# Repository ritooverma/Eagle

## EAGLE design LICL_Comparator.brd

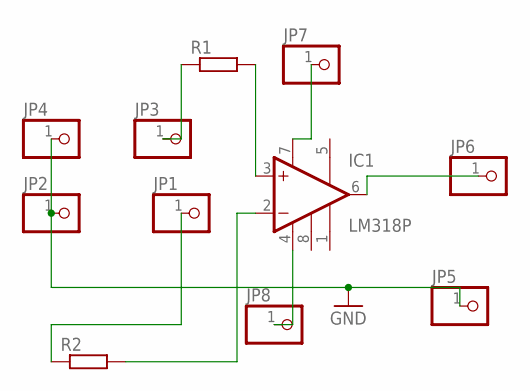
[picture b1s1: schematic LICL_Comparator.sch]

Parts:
IC1: LM318P; DIL08
JP1, JP2, JP3, JP4, JP5, JP6, JP7, JP8: PINHD-1X1; 1X01
R1, R2: R-EU_0207/10; 0207/10

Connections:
GND: JP2.1, JP4.1, JP5.1
unnamed: IC1.2 (-IN), R2.2
unnamed: IC1.3 (+IN), R1.2
unnamed: JP1.1, R2.1
unnamed: IC1.6 (OUT), JP6.1
unnamed: IC1.7 (V+), JP7.1
unnamed: IC1.4 (V-), JP8.1
unnamed: JP3.1, R1.1

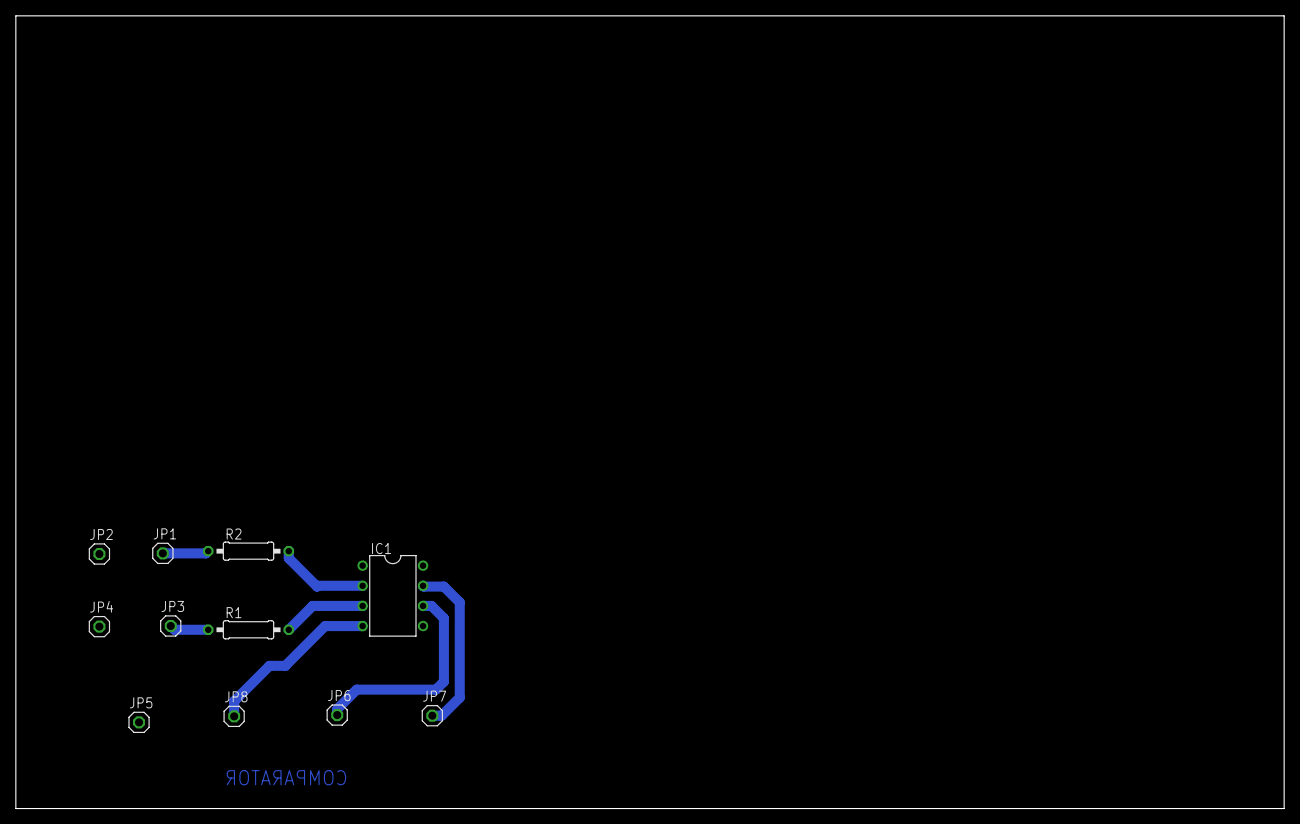
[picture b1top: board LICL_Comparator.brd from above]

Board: 2 copper layers, 160.0 x 100.0 mm, 11 parts (0 on the bottom side), 8 nets.

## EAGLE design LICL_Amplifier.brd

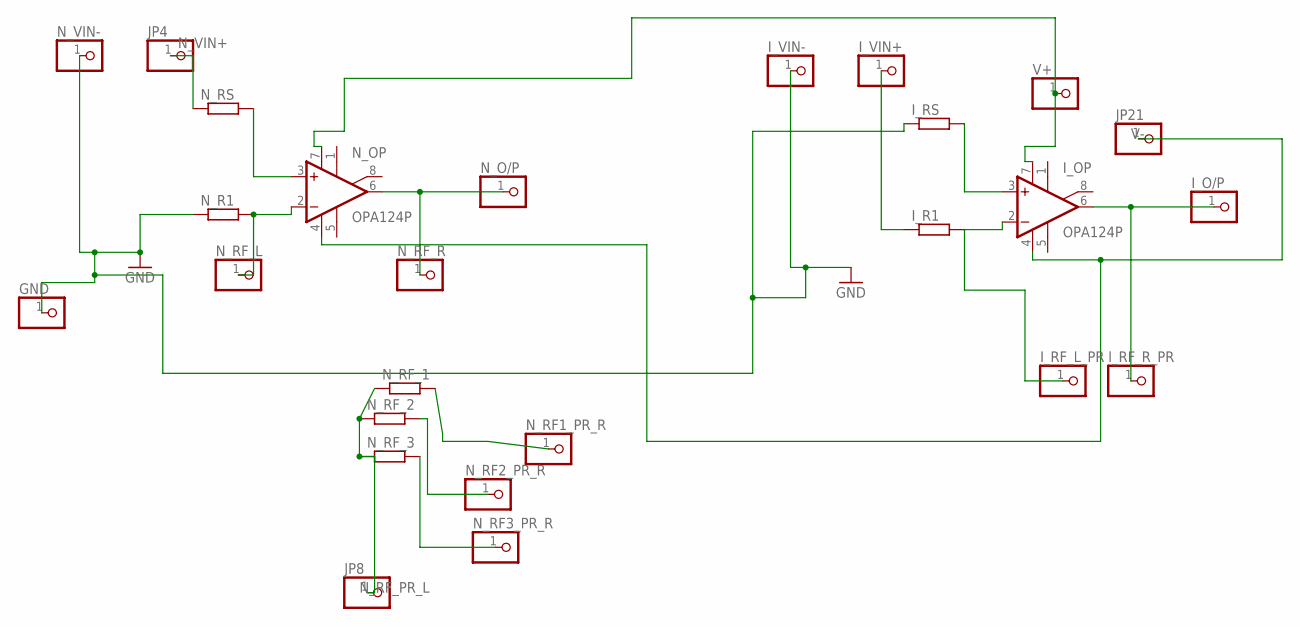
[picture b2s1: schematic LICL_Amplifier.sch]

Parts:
GND: PINHD-1X1; 1X01
I_O/P: PINHD-1X1; 1X01
I_OP: OPA124P; DIL08
I_R1: R-EU_0207/10; 0207/10
I_RF_L_PR: PINHD-1X1; 1X01
I_RF_R_PR: PINHD-1X1; 1X01
I_RS: R-EU_0207/10; 0207/10
I_VIN+: PINHD-1X1; 1X01
I_VIN-: PINHD-1X1; 1X01
JP4, JP8, JP21: PINHD-1X1; 1X01
N_O/P: PINHD-1X1; 1X01
N_OP: OPA124P; DIL08
N_R1: R-EU_0207/10; 0207/10
N_RF1_PR_R, N_RF2_PR_R, N_RF3_PR_R: PINHD-1X1; 1X01
N_RF_1, N_RF_2, N_RF_3: R-EU_0207/10; 0207/10
N_RF_L: PINHD-1X1; 1X01
N_RF_R: PINHD-1X1; 1X01
N_RS: R-EU_0207/10; 0207/10
N_VIN-: PINHD-1X1; 1X01
V+: PINHD-1X1; 1X01

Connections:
GND: GND.1, I_RS.1, I_VIN-.1, N_R1.1, N_VIN-.1
unnamed: N_OP.3 (+IN), N_RS.2
unnamed: N_O/P.1, N_OP.6 (OUT), N_RF_R.1
unnamed: N_RF1_PR_R.1, N_RF_1.2
unnamed: N_RF2_PR_R.1, N_RF_2.2
unnamed: N_RF3_PR_R.1, N_RF_3.2
unnamed: I_OP.7 (V+), N_OP.7 (V+), V+.1
unnamed: I_OP.3 (+IN), I_RS.2
unnamed: I_R1.1, I_VIN+.1
unnamed: I_OP.2 (-IN), I_R1.2, I_RF_L_PR.1
unnamed: I_O/P.1, I_OP.6 (OUT), I_RF_R_PR.1
N_RF_L: N_OP.2 (-IN), N_R1.2, N_RF_L.1
N_RF_PR_L: JP8.1, N_RF_1.1, N_RF_2.1, N_RF_3.1
N_VIN+: JP4.1, N_RS.1
V-: I_OP.4 (V-), JP21.1, N_OP.4 (V-)

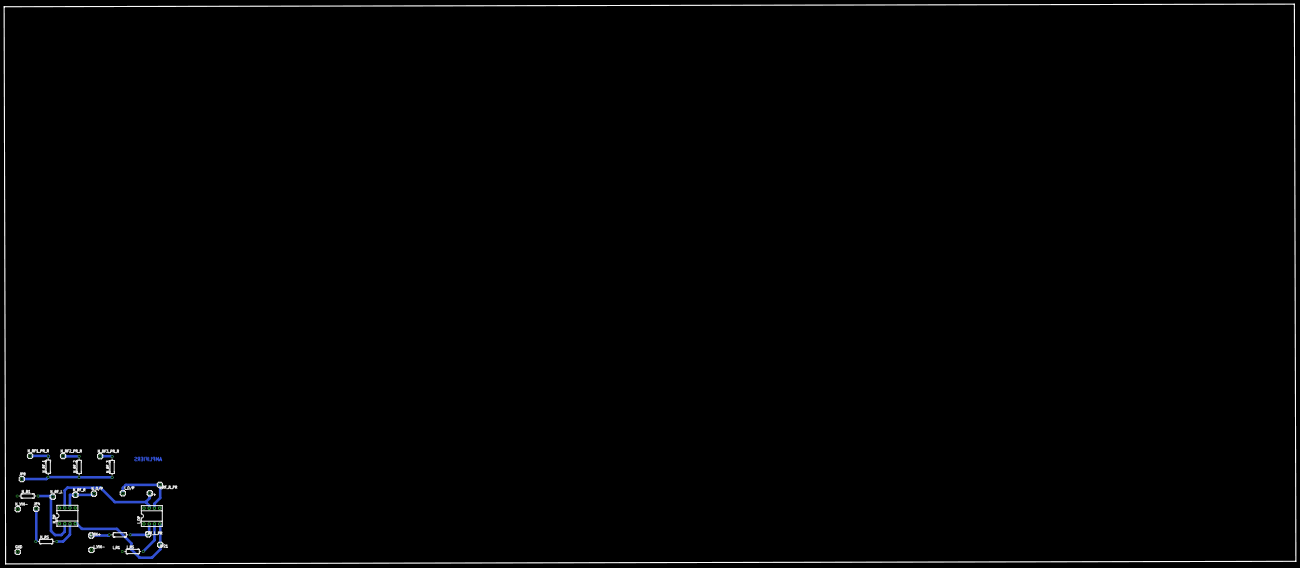
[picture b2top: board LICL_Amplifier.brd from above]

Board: 2 copper layers, 626.8 x 271.6 mm, 26 parts (0 on the bottom side), 15 nets.

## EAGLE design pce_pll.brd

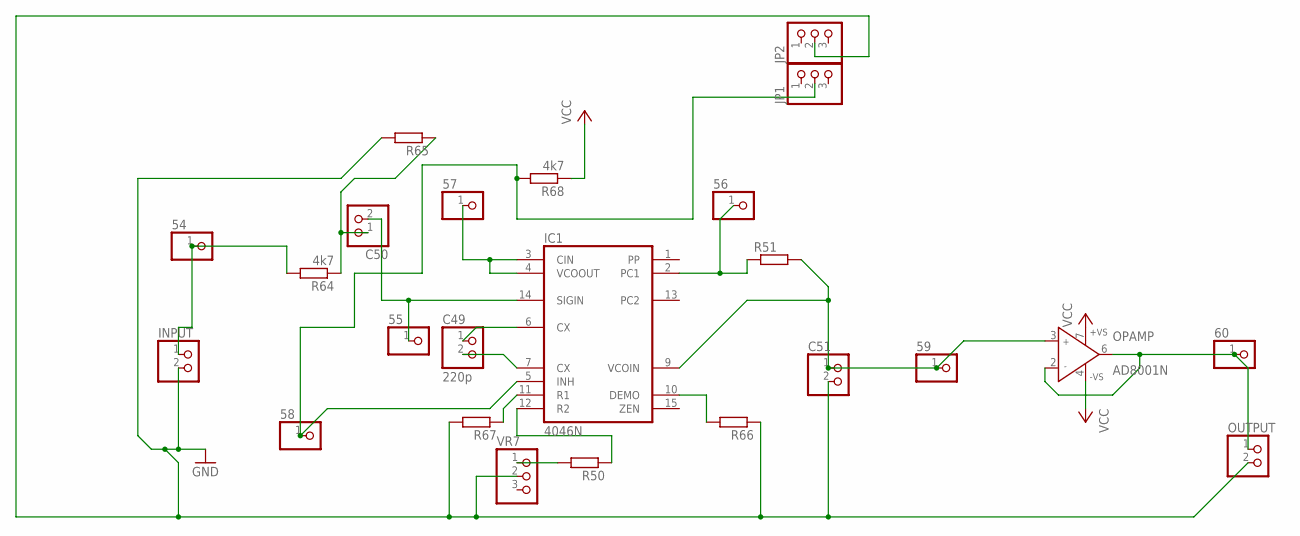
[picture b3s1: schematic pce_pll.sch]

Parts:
54, 55, 56, 57, 58, 59, 60: PINHD-1X1; 1X01
C49: 220p; 1X02
C50, C51: PINHD-1X2; 1X02
IC1: 4046N; DIL16
INPUT: PINHD-1X2; 1X02
JP1, JP2: PINHD-1X3; 1X03
OPAMP: AD8001N; DIL08
OUTPUT: PINHD-1X2; 1X02
R50, R51, R65, R66, R67: R-EU_0207/10; 0207/10
R64, R68: 4k7; 0207/10
VR7: PINHD-1X3; 1X03

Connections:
54: 54.1, INPUT.1, R64.2
GND: C51.2, INPUT.2, JP2.2, OUTPUT.2, R65.2, R66.1, R67.2, VR7.2
unnamed: 57.1, IC1.3 (CIN), IC1.4 (VCOOUT)
unnamed: 56.1, IC1.2 (PC1), R51.1
unnamed: IC1.10 (DEMO), R66.2
unnamed: 55.1, C50.2, IC1.14 (SIGIN)
unnamed: C50.1, R64.1, R65.1
unnamed: C49.1, IC1.6 (CX)
unnamed: C49.2, IC1.7 (CX)
unnamed: IC1.12 (R2), R50.1
unnamed: IC1.11 (R1), R67.1
unnamed: 60.1, OPAMP.2 (IN-), OPAMP.6 (OUT), OUTPUT.1
unnamed: 59.1, C51.1, IC1.9 (VCOIN), OPAMP.3 (IN+), R51.2
unnamed: 58.1, IC1.5 (INH), JP1.2, R68.2
unnamed: R50.2, VR7.1
VCC: OPAMP.4 (-VS), OPAMP.7 (+VS), R68.1
VDD: IC1.16 (VDD)
VSS: IC1.8 (VSS)

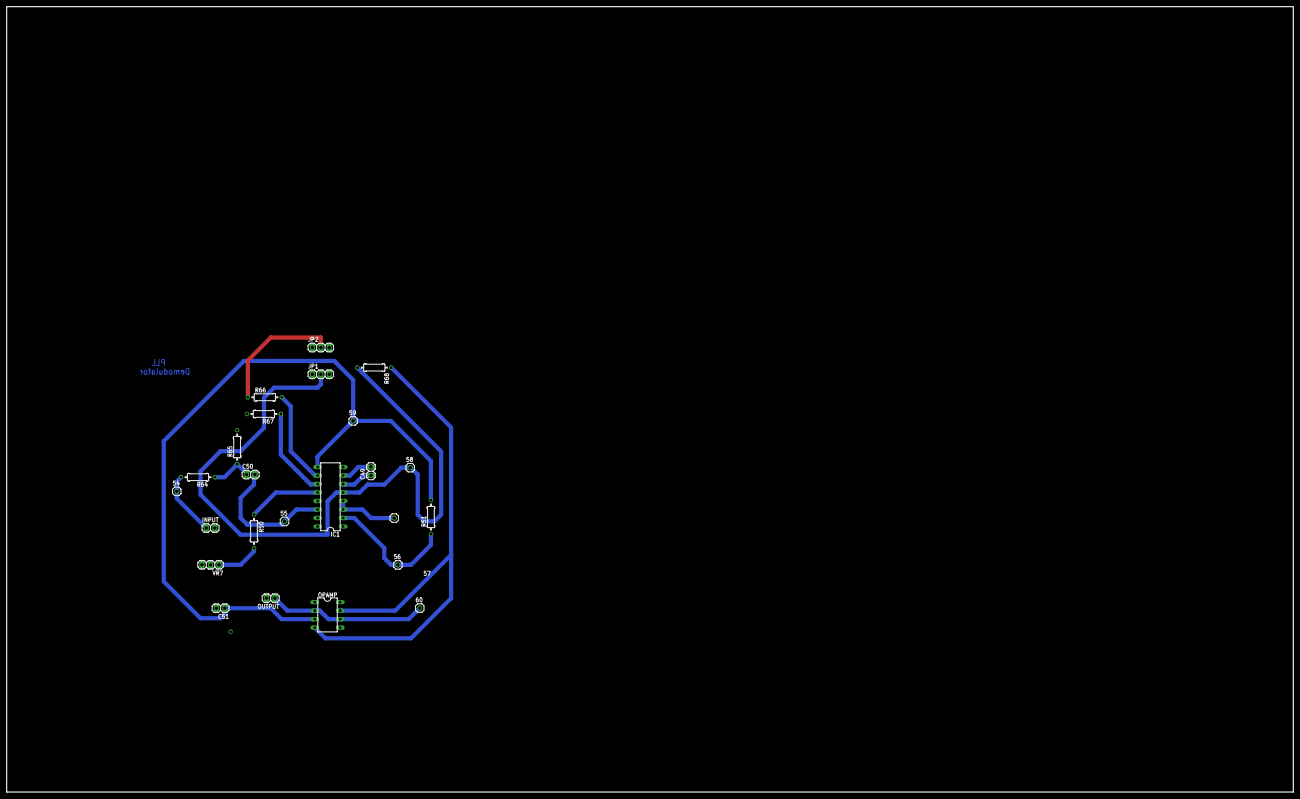
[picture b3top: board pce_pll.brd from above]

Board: 2 copper layers, 385.0 x 235.0 mm, 24 parts (0 on the bottom side), 16 nets.

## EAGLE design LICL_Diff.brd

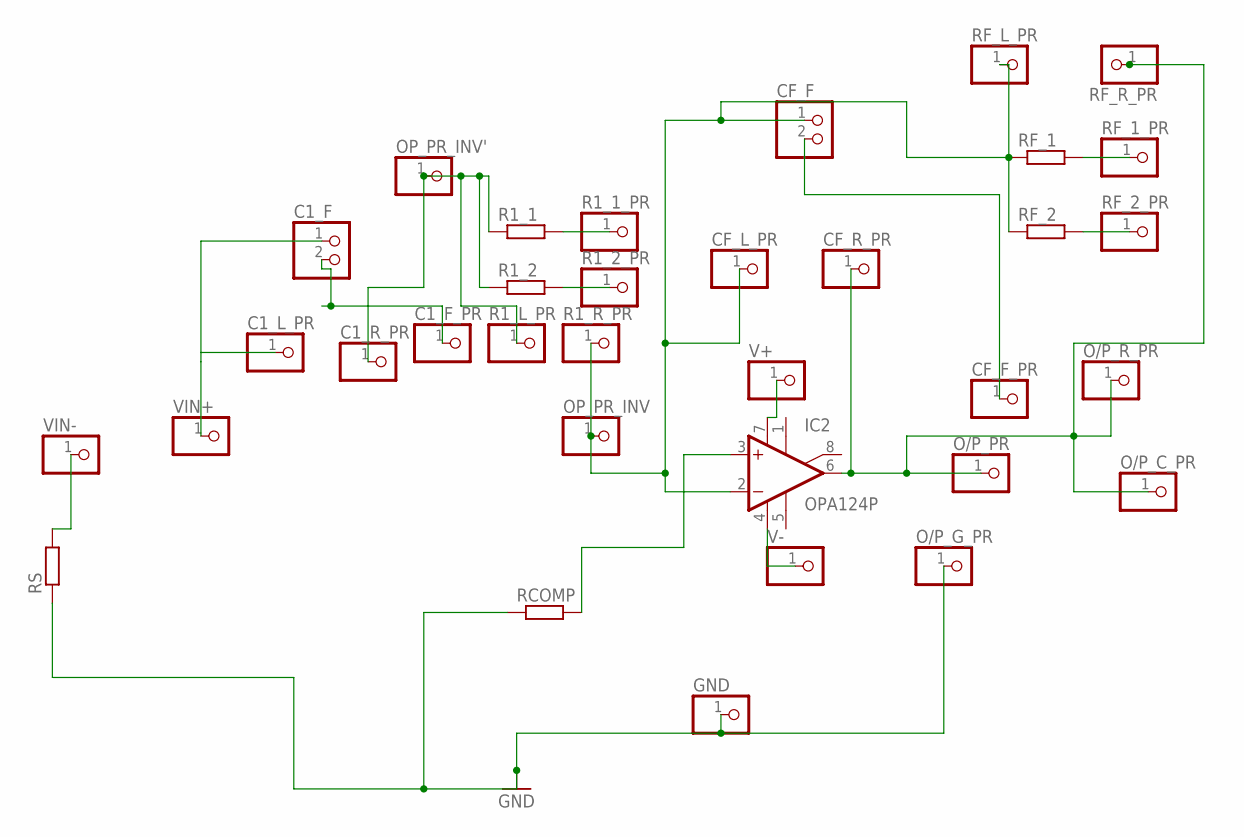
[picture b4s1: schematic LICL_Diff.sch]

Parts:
C1_F: PINHD-1X2; 1X02
C1_F_PR, C1_L_PR, C1_R_PR: PINHD-1X1; 1X01
CF_F: PINHD-1X2; 1X02
CF_F_PR: PINHD-1X1; 1X01
CF_L_PR: PINHD-1X1; 1X01
CF_R_PR: PINHD-1X1; 1X01
GND: PINHD-1X1; 1X01
IC2: OPA124P; DIL08
O/P_C_PR: PINHD-1X1; 1X01
O/P_G_PR: PINHD-1X1; 1X01
O/P_PR: PINHD-1X1; 1X01
O/P_R_PR: PINHD-1X1; 1X01
OP_PR_INV: PINHD-1X1; 1X01
OP_PR_INV': PINHD-1X1; 1X01
R1_1, R1_2: R-EU_0207/10; 0207/10
R1_1_PR, R1_2_PR, R1_L_PR, R1_R_PR: PINHD-1X1; 1X01
RCOMP: R-EU_0207/10; 0207/10
RF_1, RF_2: R-EU_0207/10; 0207/10
RF_1_PR, RF_2_PR: PINHD-1X1; 1X01
RF_L_PR: PINHD-1X1; 1X01
RF_R_PR: PINHD-1X1; 1X01
RS: R-EU_0207/10; 0207/10
V+: PINHD-1X1; 1X01
V-: PINHD-1X1; 1X01
VIN+: PINHD-1X1; 1X01
VIN-: PINHD-1X1; 1X01

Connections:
GND: GND.1, O/P_G_PR.1, RCOMP.1, RS.1
unnamed: CF_R_PR.1, IC2.6 (OUT), O/P_C_PR.1, O/P_PR.1, O/P_R_PR.1, RF_R_PR.1
unnamed: CF_F.1, CF_L_PR.1, IC2.2 (-IN), OP_PR_INV.1, R1_R_PR.1, RF_1.1, RF_2.1, RF_L_PR.1
unnamed: IC2.3 (+IN), RCOMP.2
unnamed: IC2.4 (V-), V-.1
unnamed: IC2.7 (V+), V+.1
unnamed: R1_1.2, R1_1_PR.1
unnamed: CF_F.2, CF_F_PR.1
unnamed: RF_1.2, RF_1_PR.1
unnamed: RF_2.2, RF_2_PR.1
unnamed: R1_2.2, R1_2_PR.1
unnamed: C1_F.1, C1_L_PR.1, VIN+.1
unnamed: C1_R_PR.1, OP_PR_INV'.1, R1_1.1, R1_2.1, R1_L_PR.1
unnamed: C1_F.2, C1_F_PR.1
unnamed: RS.2, VIN-.1

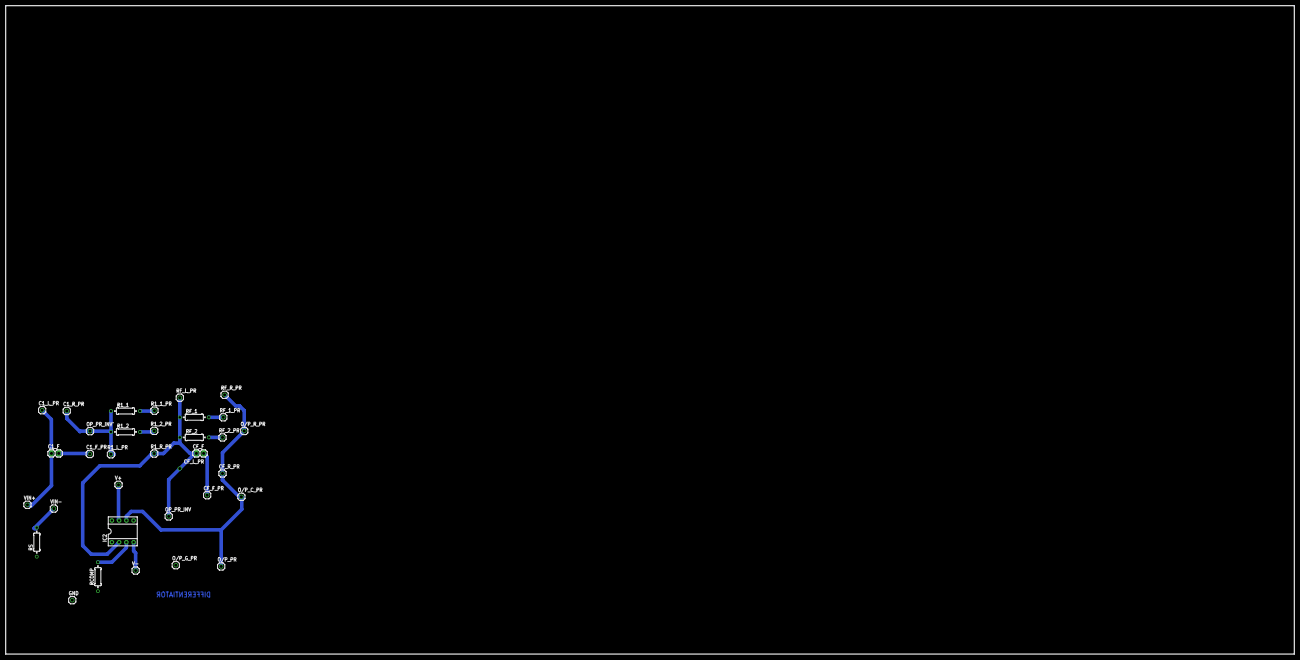
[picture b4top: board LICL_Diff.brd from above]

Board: 2 copper layers, 451.8 x 227.3 mm, 34 parts (1 on the bottom side), 15 nets.

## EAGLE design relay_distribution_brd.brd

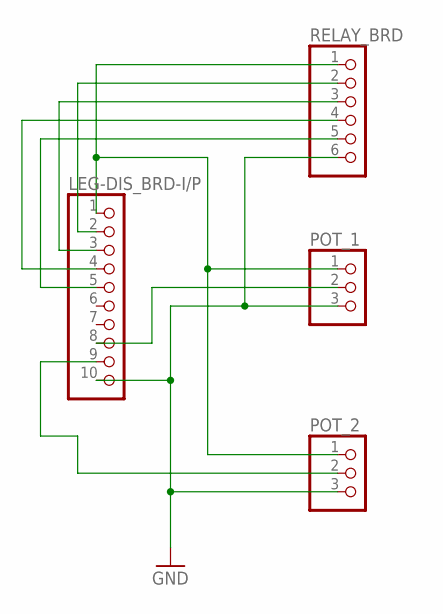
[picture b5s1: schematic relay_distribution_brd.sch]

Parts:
LEG-DIS_BRD-I/P: PINHD-1X10; 1X10
POT_1, POT_2: PINHD-1X3; 1X03
RELAY_BRD: PINHD-1X6; 1X06

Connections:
GND: LEG-DIS_BRD-I/P.10, POT_1.3, POT_2.3, RELAY_BRD.6
unnamed: LEG-DIS_BRD-I/P.1, POT_1.1, POT_2.1, RELAY_BRD.1
unnamed: LEG-DIS_BRD-I/P.9, POT_2.2
unnamed: LEG-DIS_BRD-I/P.8, POT_1.2
unnamed: LEG-DIS_BRD-I/P.2, RELAY_BRD.2
unnamed: LEG-DIS_BRD-I/P.3, RELAY_BRD.3
unnamed: LEG-DIS_BRD-I/P.5, RELAY_BRD.5
unnamed: LEG-DIS_BRD-I/P.4, RELAY_BRD.4

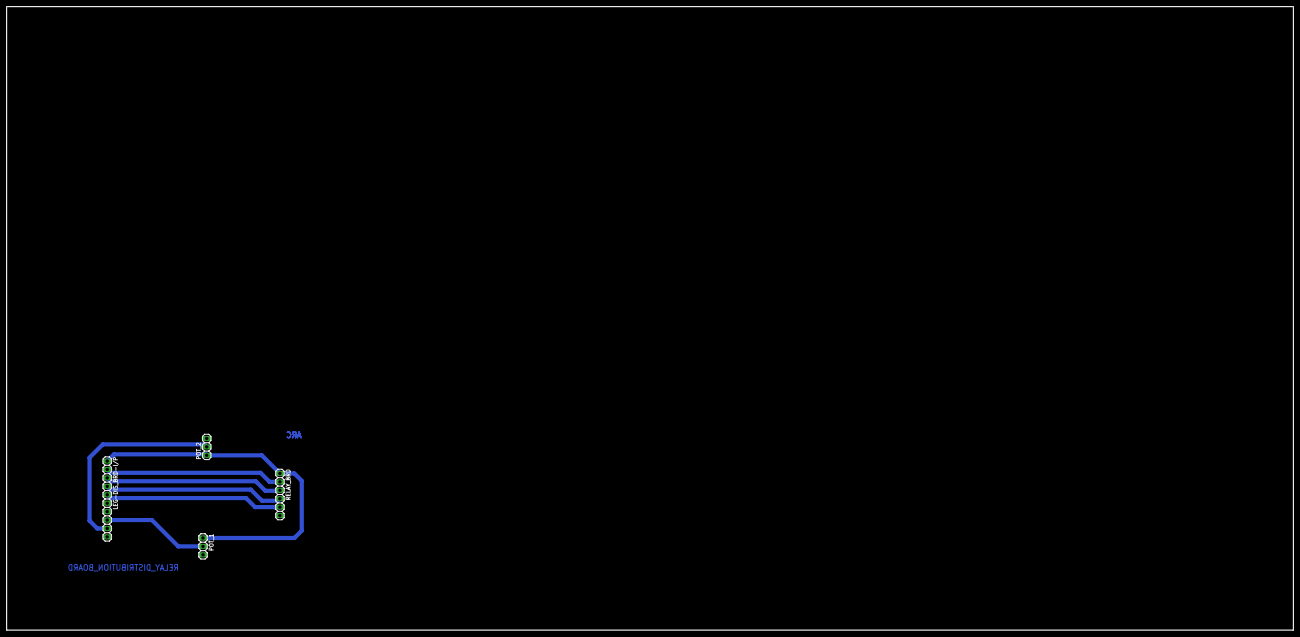
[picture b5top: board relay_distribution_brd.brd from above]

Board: 2 copper layers, 388.0 x 188.0 mm, 4 parts (0 on the bottom side), 8 nets.

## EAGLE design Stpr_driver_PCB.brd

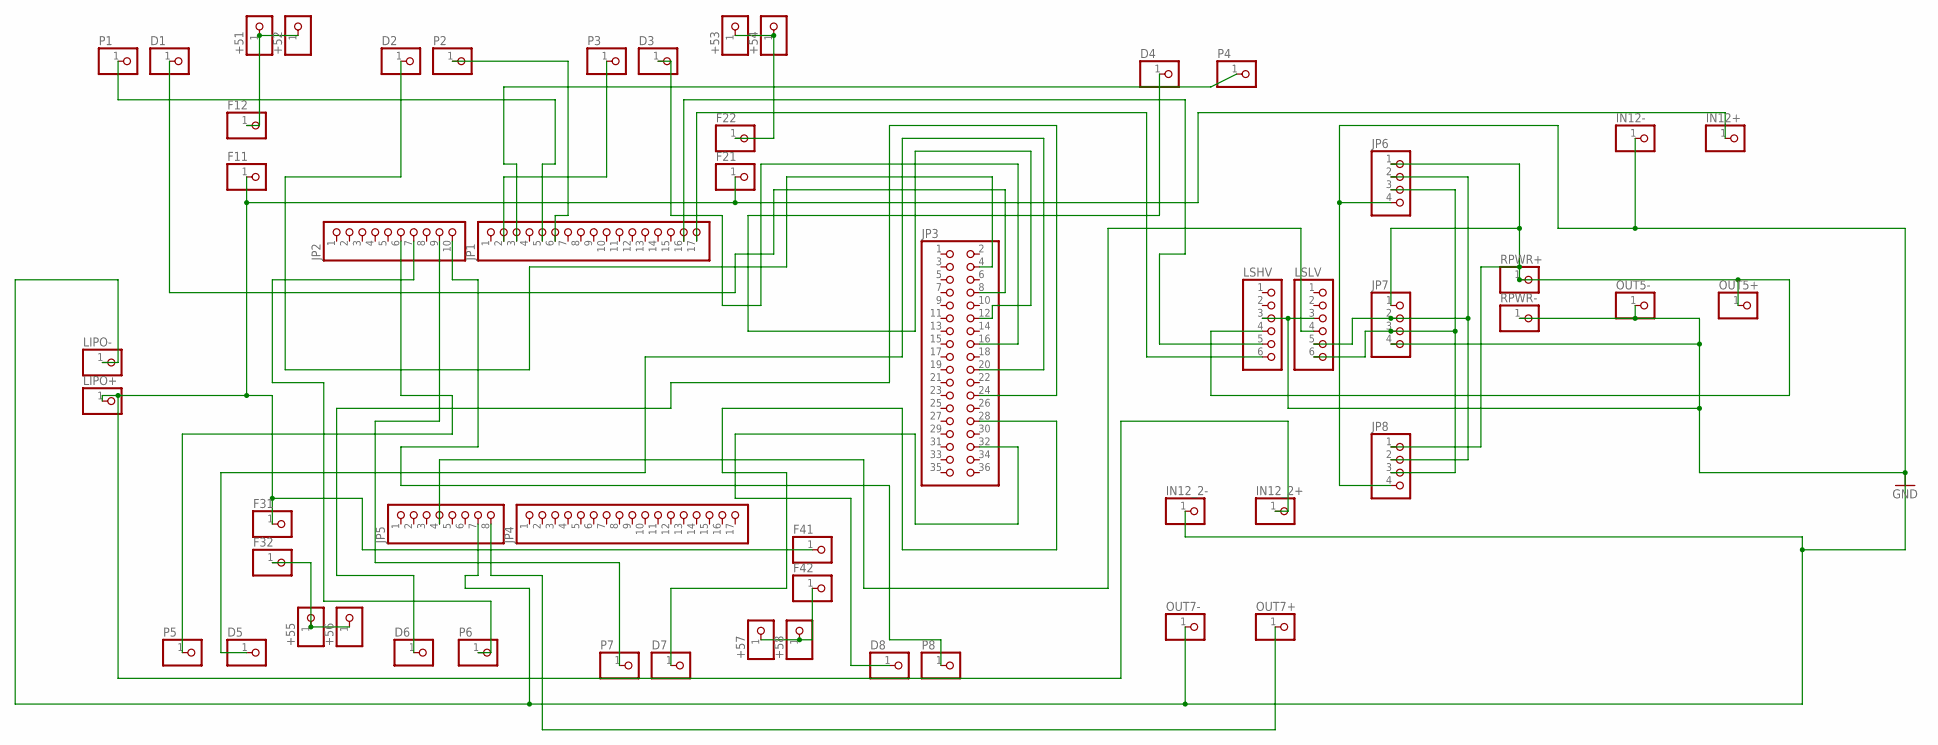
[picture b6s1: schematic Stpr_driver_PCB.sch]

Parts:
+51, +52, +53, +54, +55, +56, +57, +58: PINHD-1X1; 1X01
D1, D2, D3, D4, D5, D6, D7, D8: PINHD-1X1; 1X01
F11, F12, F21, F22, F31, F32, F41, F42: PINHD-1X1; 1X01
IN12+, IN12-, IN12_2+, IN12_2-: PINHD-1X1; 1X01
JP1, JP4: PINHD-1X17; 1X17
JP2: PINHD-1X10; 1X10
JP3: PINHD-2X18; 2X18
JP5: PINHD-1X8; 1X08
JP6, JP7, JP8: PINHD-1X4; 1X04
LIPO+: PINHD-1X1; 1X01
LIPO-: PINHD-1X1; 1X01
LSHV: PINHD-1X6; 1X06
LSLV: PINHD-1X6; 1X06
OUT5+, OUT5-, OUT7+, OUT7-: PINHD-1X1; 1X01
P1, P2, P3, P4, P5, P6, P7, P8: PINHD-1X1; 1X01
RPWR+: PINHD-1X1; 1X01
RPWR-: PINHD-1X1; 1X01

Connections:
GND: IN12-.1, IN12_2-.1, JP5.7, JP6.4, JP7.4, JP8.4, LIPO-.1, LSHV.3, LSLV.3, OUT5-.1, OUT7-.1, RPWR-.1
unnamed: F11.1, F21.1, F31.1, F41.1, IN12+.1, LIPO+.1
unnamed: +55.1, +56.1, F32.1
unnamed: +57.1, +58.1, F42.1
unnamed: +51.1, +52.1, F12.1
unnamed: +53.1, +54.1, F22.1
unnamed: D3.1, JP3.16
unnamed: JP1.5, P1.1
unnamed: JP6.1, JP7.1, JP8.1, LSHV.4, OUT5+.1, RPWR+.1
unnamed: JP1.6, P2.1
unnamed: JP1.2, P3.1
unnamed: JP1.3, P4.1
unnamed: JP2.6, P5.1
unnamed: JP6.2, JP7.2, JP8.2, LSLV.5
unnamed: JP2.9, P7.1
unnamed: JP5.8, OUT7+.1
unnamed: D1.1, JP3.8
unnamed: D2.1, JP3.4
unnamed: D4.1, JP3.12
unnamed: JP2.10, P8.1
unnamed: D5.1, JP3.20
unnamed: D6.1, JP3.24
unnamed: D7.1, JP3.28
unnamed: D8.1, JP3.32
unnamed: JP2.7, P6.1
unnamed: JP6.3, JP7.3, JP8.3, LSLV.6
unnamed: JP1.17, LSHV.6
unnamed: JP1.16, LSHV.5
unnamed: JP5.4, LSLV.4

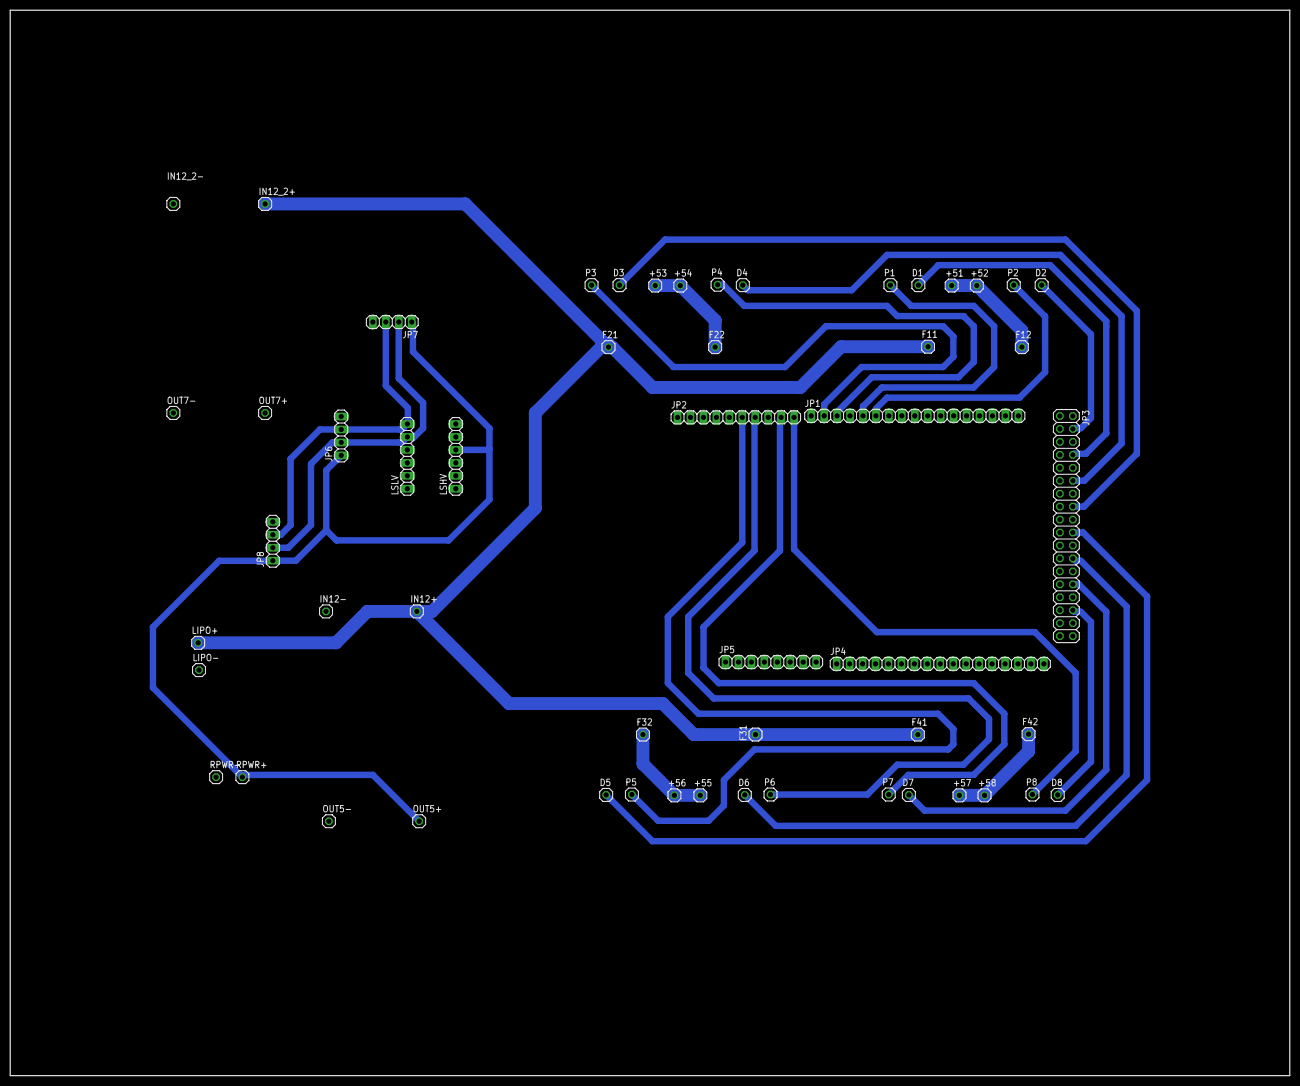
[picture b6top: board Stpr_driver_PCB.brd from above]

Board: 2 copper layers, 251.0 x 209.0 mm, 54 parts (0 on the bottom side), 29 nets.

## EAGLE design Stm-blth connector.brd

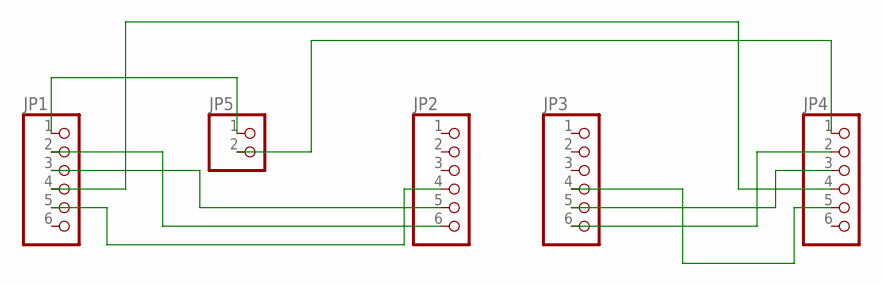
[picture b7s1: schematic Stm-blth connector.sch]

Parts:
JP1, JP2, JP3, JP4: PINHD-1X6; 1X06
JP5: PINHD-1X2; 1X02

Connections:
GND: JP1.4, JP4.4
unnamed: JP1.1, JP5.1
unnamed: JP4.1, JP5.2
unnamed: JP1.2, JP2.6
unnamed: JP3.6, JP4.2
unnamed: JP1.3, JP2.5
unnamed: JP3.5, JP4.3
unnamed: JP1.5, JP2.4
unnamed: JP3.4, JP4.5

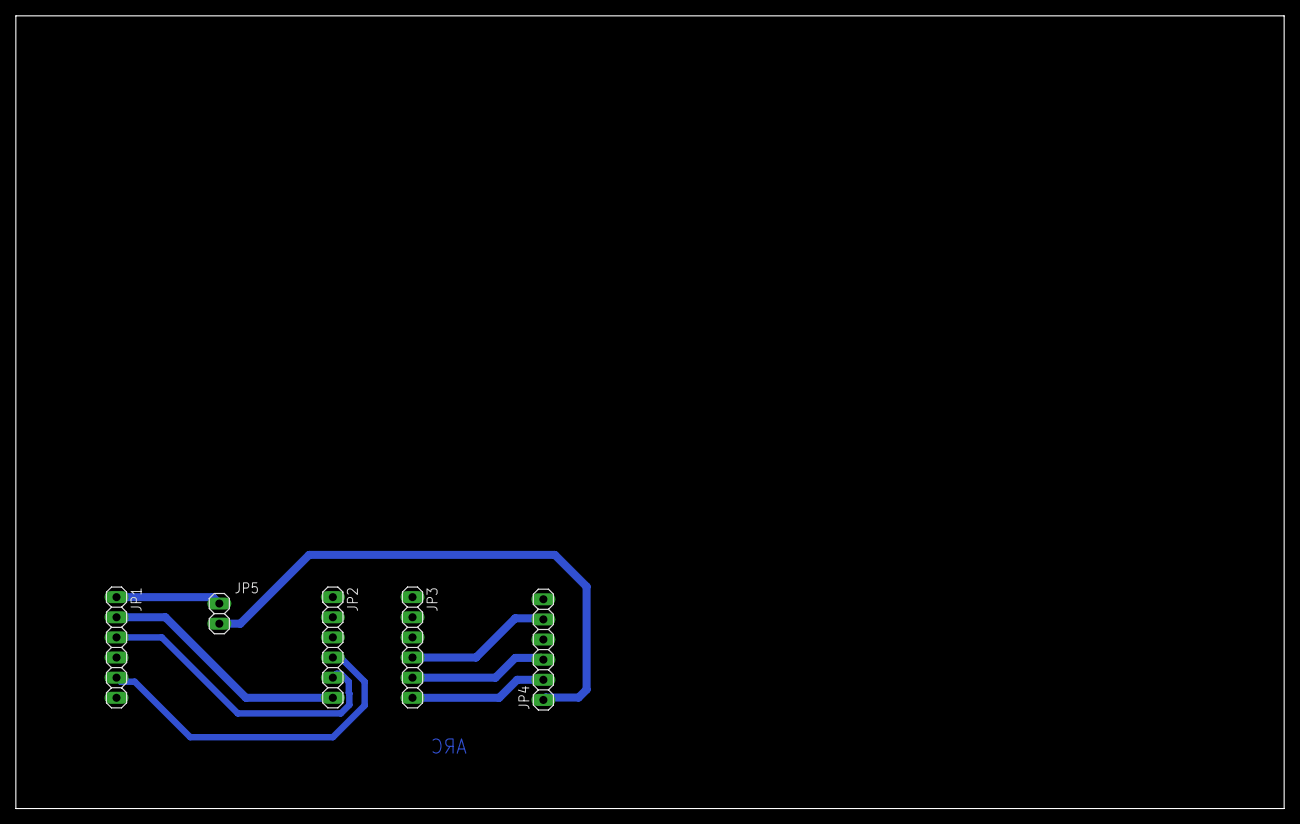
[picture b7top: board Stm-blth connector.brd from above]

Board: 2 copper layers, 160.0 x 100.0 mm, 5 parts (0 on the bottom side), 9 nets.

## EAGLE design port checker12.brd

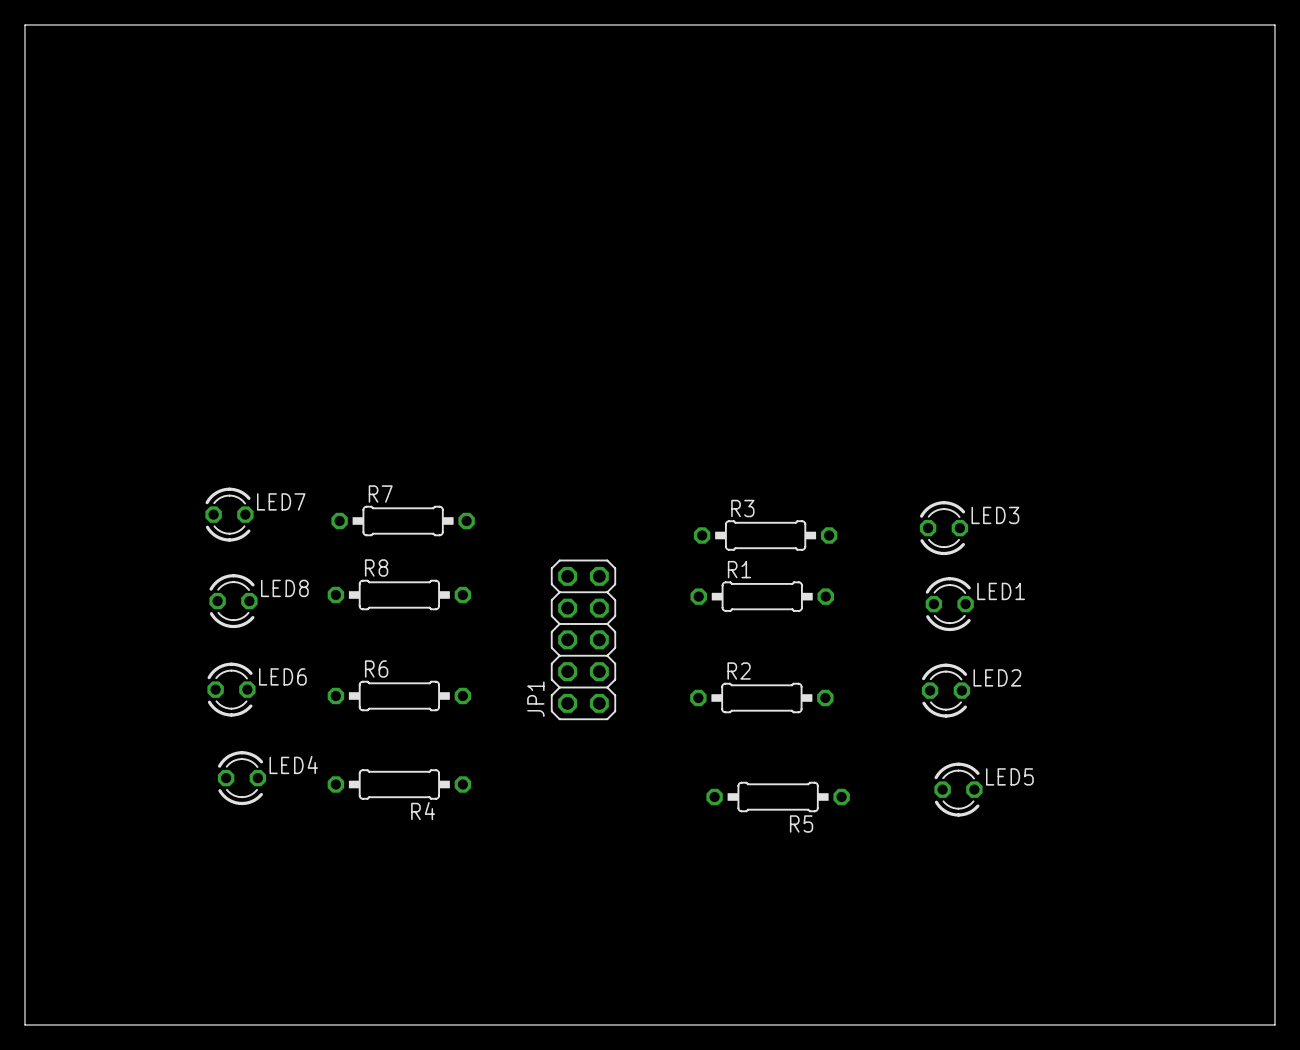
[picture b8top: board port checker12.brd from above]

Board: 2 copper layers, 100.0 x 80.0 mm, 17 parts (0 on the bottom side), 17 nets, no tracks yet.

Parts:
JP1: 2X05
LED1, LED2, LED3, LED4, LED5, LED6, LED7, LED8: LED3MM
R1, R2, R3, R4, R5, R6, R7, R8: 0207/10

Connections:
GND: JP1.10, LED1.K, LED2.K, LED3.K, LED4.K, LED5.K, LED6.K, LED7.K, LED8.K
unnamed: JP1.1, R5.2
unnamed: JP1.3, R6.2
unnamed: JP1.5, R7.2
unnamed: JP1.7, R8.2
unnamed: JP1.2, R1.1
unnamed: JP1.4, R2.1
unnamed: JP1.6, R3.1
unnamed: JP1.8, R4.1
unnamed: LED5.A, R5.1
unnamed: LED6.A, R6.1
unnamed: LED7.A, R7.1
unnamed: LED8.A, R8.1
unnamed: LED1.A, R1.2
unnamed: LED2.A, R2.2
unnamed: LED3.A, R3.2
unnamed: LED4.A, R4.2

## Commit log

2019-03-16 Add files via upload
    PCBs
2019-03-16 Set theme jekyll-theme-cayman
